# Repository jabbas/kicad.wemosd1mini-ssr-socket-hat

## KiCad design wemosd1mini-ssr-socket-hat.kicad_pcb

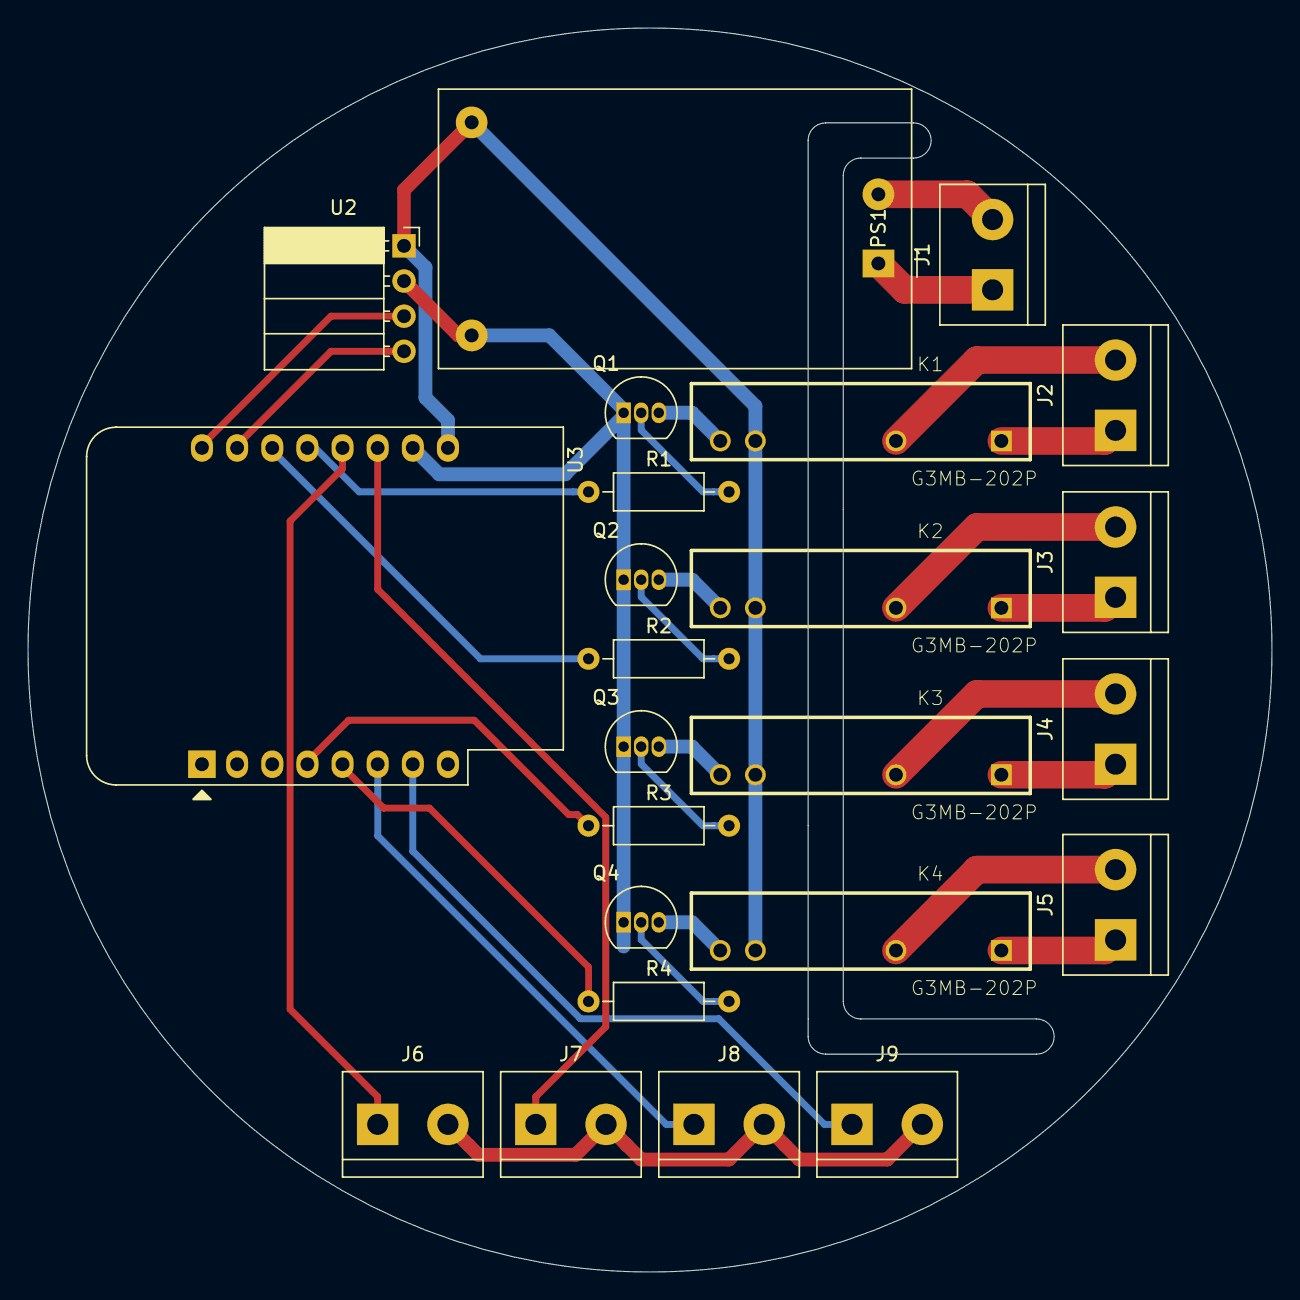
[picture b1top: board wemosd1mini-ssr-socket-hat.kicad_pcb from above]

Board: 2 copper layers, 89.9 x 89.9 mm, 24 parts (0 on the bottom side), 30 nets.

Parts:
J1, J2, J3, J4, J5, J6, J7, J8, J9: Screw_Terminal_01x02; TerminalBlock_bornier-2_P5.08mm
K1, K2, K3, K4: G3MB-202P; RELAY_G3MB-202P
PS1: HLK-PM01; Converter_ACDC_HiLink_HLK-PMxx
Q1, Q2, Q3, Q4: BC547; TO-92_Inline
R1, R2, R3, R4: R; R_Axial_DIN0207_L6.3mm_D2.5mm_P10.16mm_Horizontal
U2: SHT3x-HAT; PinSocket_1x04_P2.54mm_Horizontal
U3: WeMos_D1_mini; WEMOS_D1_mini_light

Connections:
+5V: K1.3, K2.3, K3.3, K4.3, PS1.4, U2.1, U3.9
GND: J6.2, J7.2, J8.2, J9.2, PS1.3, Q1.1, Q2.1, Q3.1, Q4.1, U2.2, U3.10
unnamed: J1.1, PS1.1
unnamed: J1.2, PS1.2
unnamed: J2.1, K1.1
unnamed: J2.2, K1.2
unnamed: J3.1, K2.1
unnamed: J3.2, K2.2
unnamed: J4.1, K3.1
unnamed: J4.2, K3.2
unnamed: J5.1, K4.1
unnamed: J5.2, K4.2
unnamed: J6.1, U3.12
unnamed: J7.1, U3.11
unnamed: J8.1, U3.6
unnamed: J9.1, U3.7
unnamed: K1.4, Q1.3
unnamed: K2.4, Q2.3
unnamed: K3.4, Q3.3
unnamed: K4.4, Q4.3
unnamed: Q1.2, R1.2
unnamed: Q2.2, R2.2
unnamed: Q3.2, R3.2
unnamed: Q4.2, R4.2
unnamed: R1.1, U3.13
unnamed: R2.1, U3.14
unnamed: R3.1, U3.4
unnamed: R4.1, U3.5
unnamed: U2.3, U3.16
unnamed: U2.4, U3.15
